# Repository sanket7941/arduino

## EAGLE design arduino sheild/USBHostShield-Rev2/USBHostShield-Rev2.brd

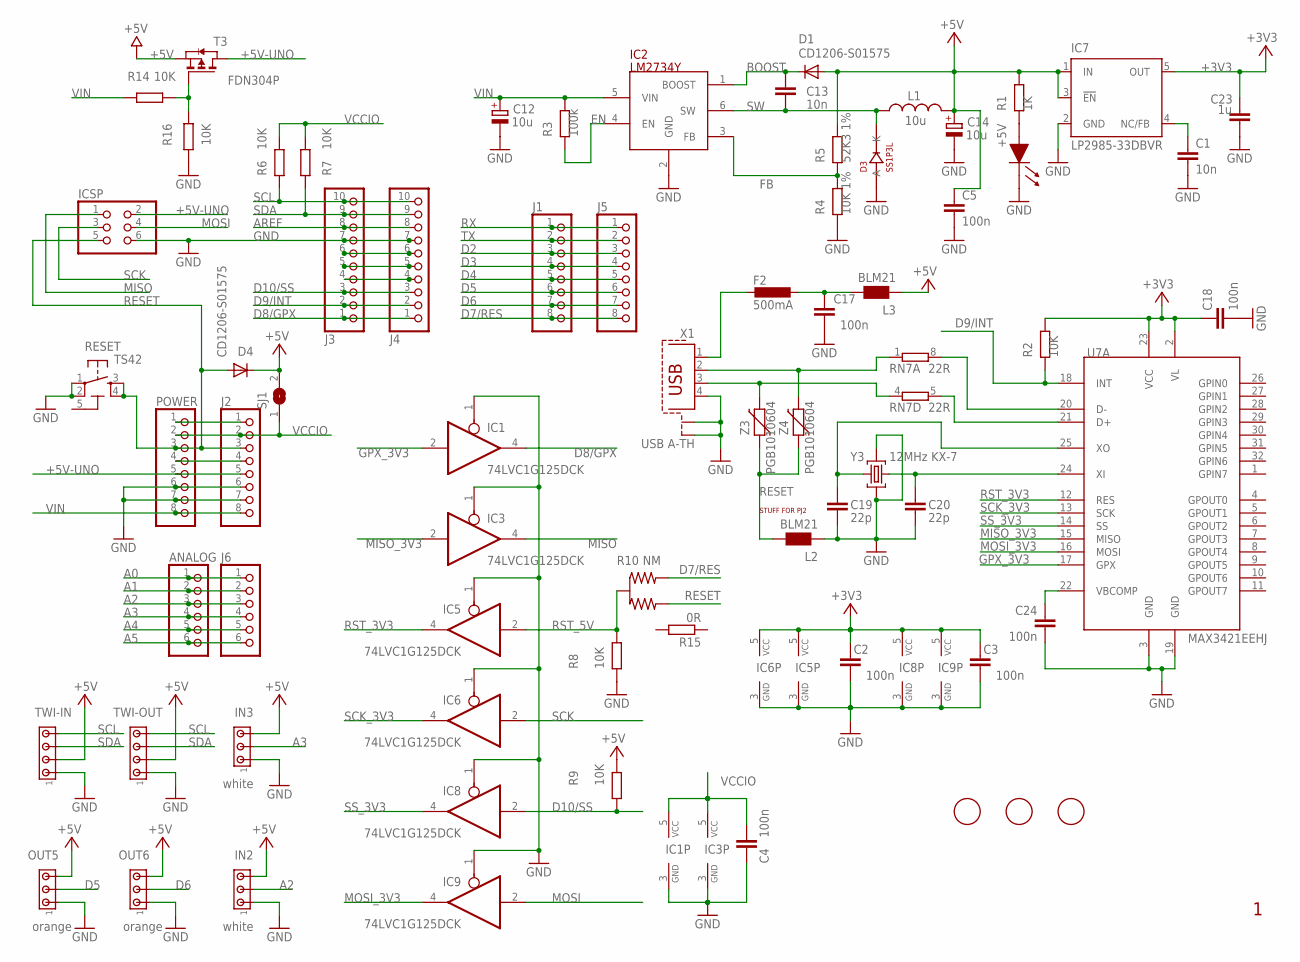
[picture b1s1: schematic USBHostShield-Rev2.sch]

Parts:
+5V: MYSMD_LED0805; SMD_LED0805
ANALOG: PINHD-1X6TH; 1X06-TH
C1, C13: 10n; C0603-ROUND
C2, C3, C4, C5, C17, C18, C24: 100n; C0603-ROUND
C12, C14: 10u; SMC_B
C19, C20: 22p; C0603-ROUND
C23: 1u; C0603-ROUND
D1, D4: CD1206-S01575; MINIMELF
D3: SS1P3L; DO220AAL
F2: 500mA; L1812
IC1, IC3, IC5, IC6, IC8, IC9: 74LVC1G125DCK; SC70-5
IC2: LM2734Y; SOT23-6
IC7: LP2985-33DBVR; SOT23-DBV
ICSP: PINHD-2X3; 2X03
IN2, IN3: white; 10X03MTA
J1, J2, J5: PINHD-1X8TH; 1X08-TH
J3, J4: PINHD-1X10TH; 1X10-TH
J6: PINHD-1X6TH; 1X06-TH
L1: 10u; SRR0604
L2, L3: BLM21; 0805
OUT5, OUT6: orange; 10X03MTA
POWER: PINHD-1X8TH; 1X08-TH
R1: 1K; R0603-ROUND
R2, R6, R7, R8, R9, R14, R16: 10K; R0603-ROUND
R3: 100k; R0603-ROUND
R4: 10K 1%; R0603-ROUND
R5: 52K3 1%; R0603-ROUND
R10: NM; J0402
R15: 0R; R0402
RESET: TS42
RN7: 22R; CAY16
SJ1: SJ
T3: FDN304P; SOT-23
TWI-IN: 0205_LHA-04-TS__4X1_VERTICALE_BIANCO_P_2,54; 10X04MTA
TWI-OUT: 0205_LHA-04-TS__4X1_VERTICALE_BIANCO_P_2,54; 10X04MTA
U7A: MAX3421EEHJ; TQFP32-05
U$1, U$3, U$6: FIDUCIALMOUNT; FIDUCIA-MOUNT
X1: USB A-TH; PN87520-S
Y3: 12MHz KX-7; CRYSTAL-3.2-2.5
Z3, Z4: PGB1010604; CT/CN0603

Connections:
5-GND: RESET.5 (5-GND)
+3V3: C2.1, C3.1, C18.1, C23.2, IC5.5 (VCC), IC6.5 (VCC), IC7.5 (OUT), IC8.5 (VCC), IC9.5 (VCC), R2.1, U7A.2 (VL), U7A.23 (VCC)
+5V: C5.1, C14.+, D1.A, D4.C, IC7.1 (IN), IC7.3 (!EN), IN2.3, IN3.3, L1.P$2 (2), L3.1, OUT5.3, OUT6.3, R1.1, R5.1, R9.1, SJ1.2, T3.2 (S), TWI-IN.2, TWI-OUT.2
+5V-UNO: ICSP.2, J2.5, POWER.5, T3.1 (D)
A0: ANALOG.1, J6.1
A1: ANALOG.2, J6.2
A2: ANALOG.3, IN2.2, J6.3
A3: ANALOG.4, IN3.2, J6.4
A4: ANALOG.5, J6.5
A5: ANALOG.6, J6.6
AREF: J3.8, J4.8
BOOST: C13.1, D1.C, IC2.1 (BOOST)
D2: J1.3, J5.3
D3: J1.4, J5.4
D4: J1.5, J5.5
D5: J1.6, J5.6, OUT5.2
D6: J1.7, J5.7, OUT6.2
D7/RES: J1.8, J5.8, R10.1
D8/GPX: IC1.4 (O), J3.1, J4.1
D9/INT: J3.2, J4.2, R2.2, U7A.18 (INT)
D10/SS: IC8.2 (I), J3.3, J4.3, R9.2
EN: IC2.4 (EN), R3.2
FB: IC2.3 (FB), R4.1, R5.2
GND: +5V.1 (CA), C1.2, C2.2, C3.2, C4.2, C5.2, C12.-, C14.-, C17.2, C18.2, C19.1, C20.1, C23.1, C24.2, D3.P$2 (A), IC1.1 (OE), IC1.3 (GND), IC2.2 (GND), IC3.1 (OE), IC3.3 (GND), IC5.1 (OE), IC5.3 (GND), IC6.1 (OE), IC6.3 (GND), IC7.2 (GND), IC8.1 (OE), IC8.3 (GND), IC9.1 (OE), IC9.3 (GND), ICSP.6, IN2.1, IN3.1, J2.6, J2.7, J3.7, J4.7, L2.1, OUT5.1, OUT6.1, POWER.6, POWER.7, R4.2, R8.2, R16.1, RESET.1, RESET.2, TWI-IN.1, TWI-OUT.1, U7A.3 (GND), U7A.19 (GND), X1.4, X1.S1, X1.S2, Y3.2 (GND), Y3.4 (GND)
GPX_3V3: IC1.2 (I), U7A.17 (GPX)
MISO: IC3.4 (O), ICSP.1
MISO_3V3: IC3.2 (I), U7A.15 (MISO)
MOSI: IC9.2 (I), ICSP.4
MOSI_3V3: IC9.4 (O), U7A.16 (MOSI)
unnamed: C1.1, IC7.4 (NC/FB)
unnamed: +5V.2 (AN), R1.2
unnamed: L2.2, Z3.1, Z4.1
unnamed: R14.2, R16.2, T3.3 (G)
unnamed: J2.4, POWER.4
unnamed: J3.4, J4.4
unnamed: J3.5, J4.5
unnamed: J3.6, J4.6
unnamed: RN7.1, X1.2, Z4.2
unnamed: RN7.4 (1), X1.3, Z3.2
unnamed: RN7.8 (2), U7A.20 (D-)
unnamed: RN7.5 (2), U7A.21 (D+)
unnamed: C20.2, U7A.24 (XI), Y3.1 (C1)
unnamed: C19.2, U7A.25 (XO), Y3.3 (C2)
unnamed: F2.2, X1.1
unnamed: C17.1, F2.1, L3.2
unnamed: J2.1, POWER.1
unnamed: C24.1, U7A.22 (VBCOMP)
RESET: D4.A, ICSP.5, J2.3, POWER.3, R10.3 (2), RESET.3, RESET.4
RST_3V3: IC5.4 (O), U7A.12 (RES)
RST_5V: IC5.2 (I), R8.1, R10.2 (C)
RX: J1.1, J5.1
SCK: IC6.2 (I), ICSP.3
SCK_3V3: IC6.4 (O), U7A.13 (SCK)
SCL: J3.10, J4.10, R6.2, TWI-IN.4, TWI-OUT.4
SDA: J3.9, J4.9, R7.2, TWI-IN.3, TWI-OUT.3
SS_3V3: IC8.4 (O), U7A.14 (SS)
SW: C13.2, D3.P$1 (K), IC2.6 (SW), L1.P$1 (1)
TX: J1.2, J5.2
VCCIO: C4.1, IC1.5 (VCC), IC3.5 (VCC), J2.2, POWER.2, R6.1, R7.1, SJ1.1
VIN: C12.+, IC2.5 (VIN), J2.8, POWER.8, R3.1, R14.1

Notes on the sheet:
STUFF FOR PJ2

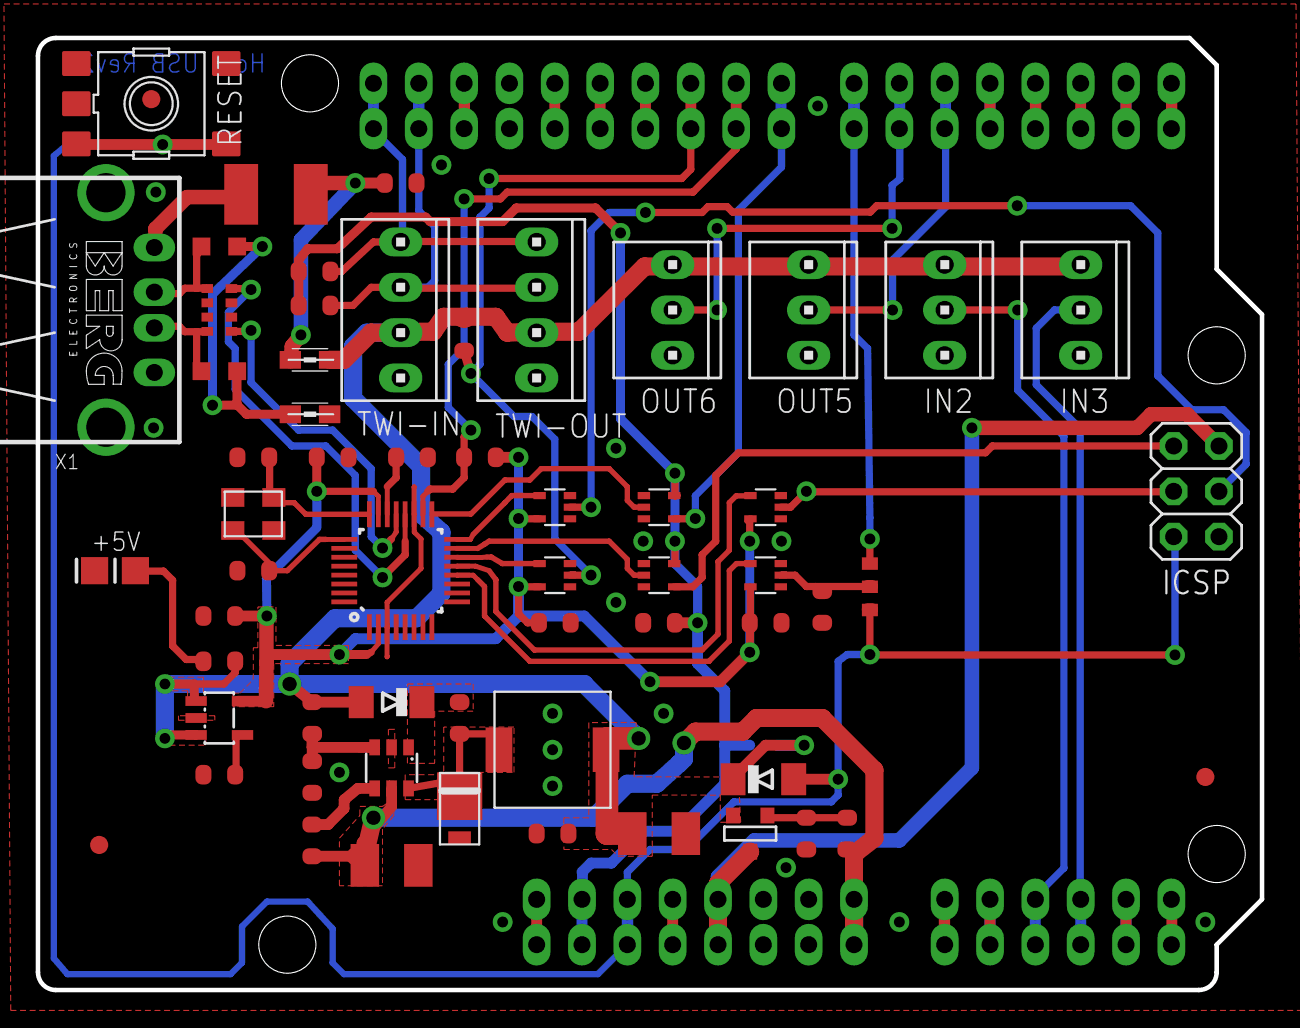
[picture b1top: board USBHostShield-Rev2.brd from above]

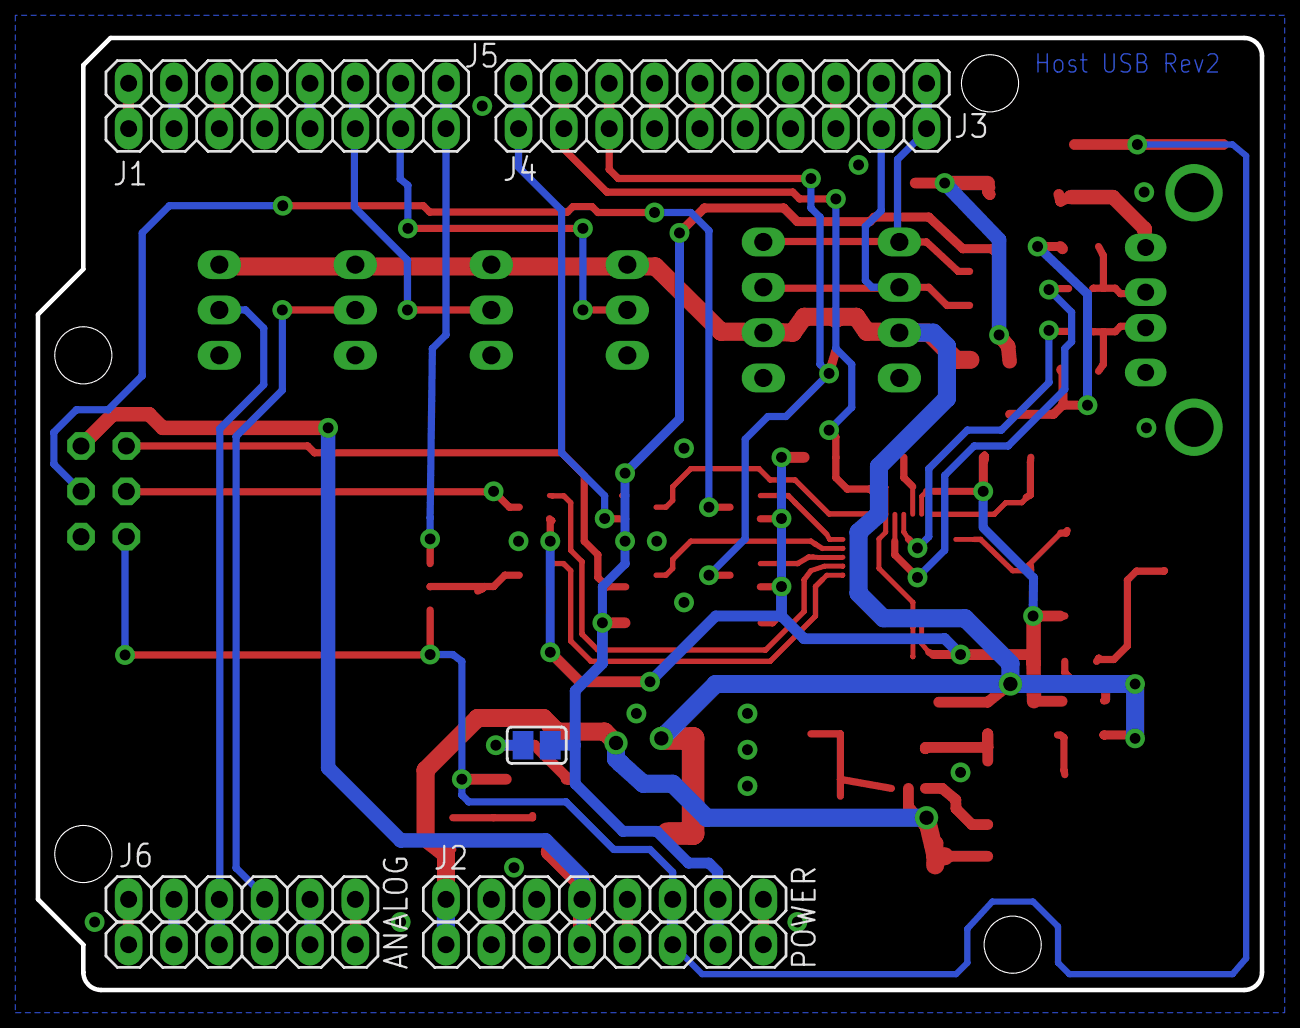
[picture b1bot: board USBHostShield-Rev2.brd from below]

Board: 2 copper layers, 68.6 x 53.3 mm, 70 parts (9 on the bottom side), 59 nets.

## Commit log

2017-06-30 arduino sheild added
2017-07-02 add lib
2017-07-03 new folder arduino project
2017-07-04 clock code uploade
2017-07-04 one sheeld
2017-07-05 7seg
2017-07-06 servo
2017-07-10 ping
2017-07-11 gayro added
2017-07-13 potentio meter
